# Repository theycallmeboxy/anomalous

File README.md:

# Anomalous Keyboard

## Features

- Integrated STM32 Microcontroller
  
- 42 Key Alice-ish Ortho Layout

- Red Dragon Low Profile Switches

- Solder Only

## Repository Contents

- `pcb/`: KiCAD and production files (bom is missing part numbers)

## Status

- Prototype 1 PCBs ordered 3/15/2024
- Prototype 1 PCBs received 3/20/2024

**DISCLAIMER: I'm not a doctor.  This is not medical advice.  I'm also only a network engineer.  You assume all liability in using or reproducing these files.**

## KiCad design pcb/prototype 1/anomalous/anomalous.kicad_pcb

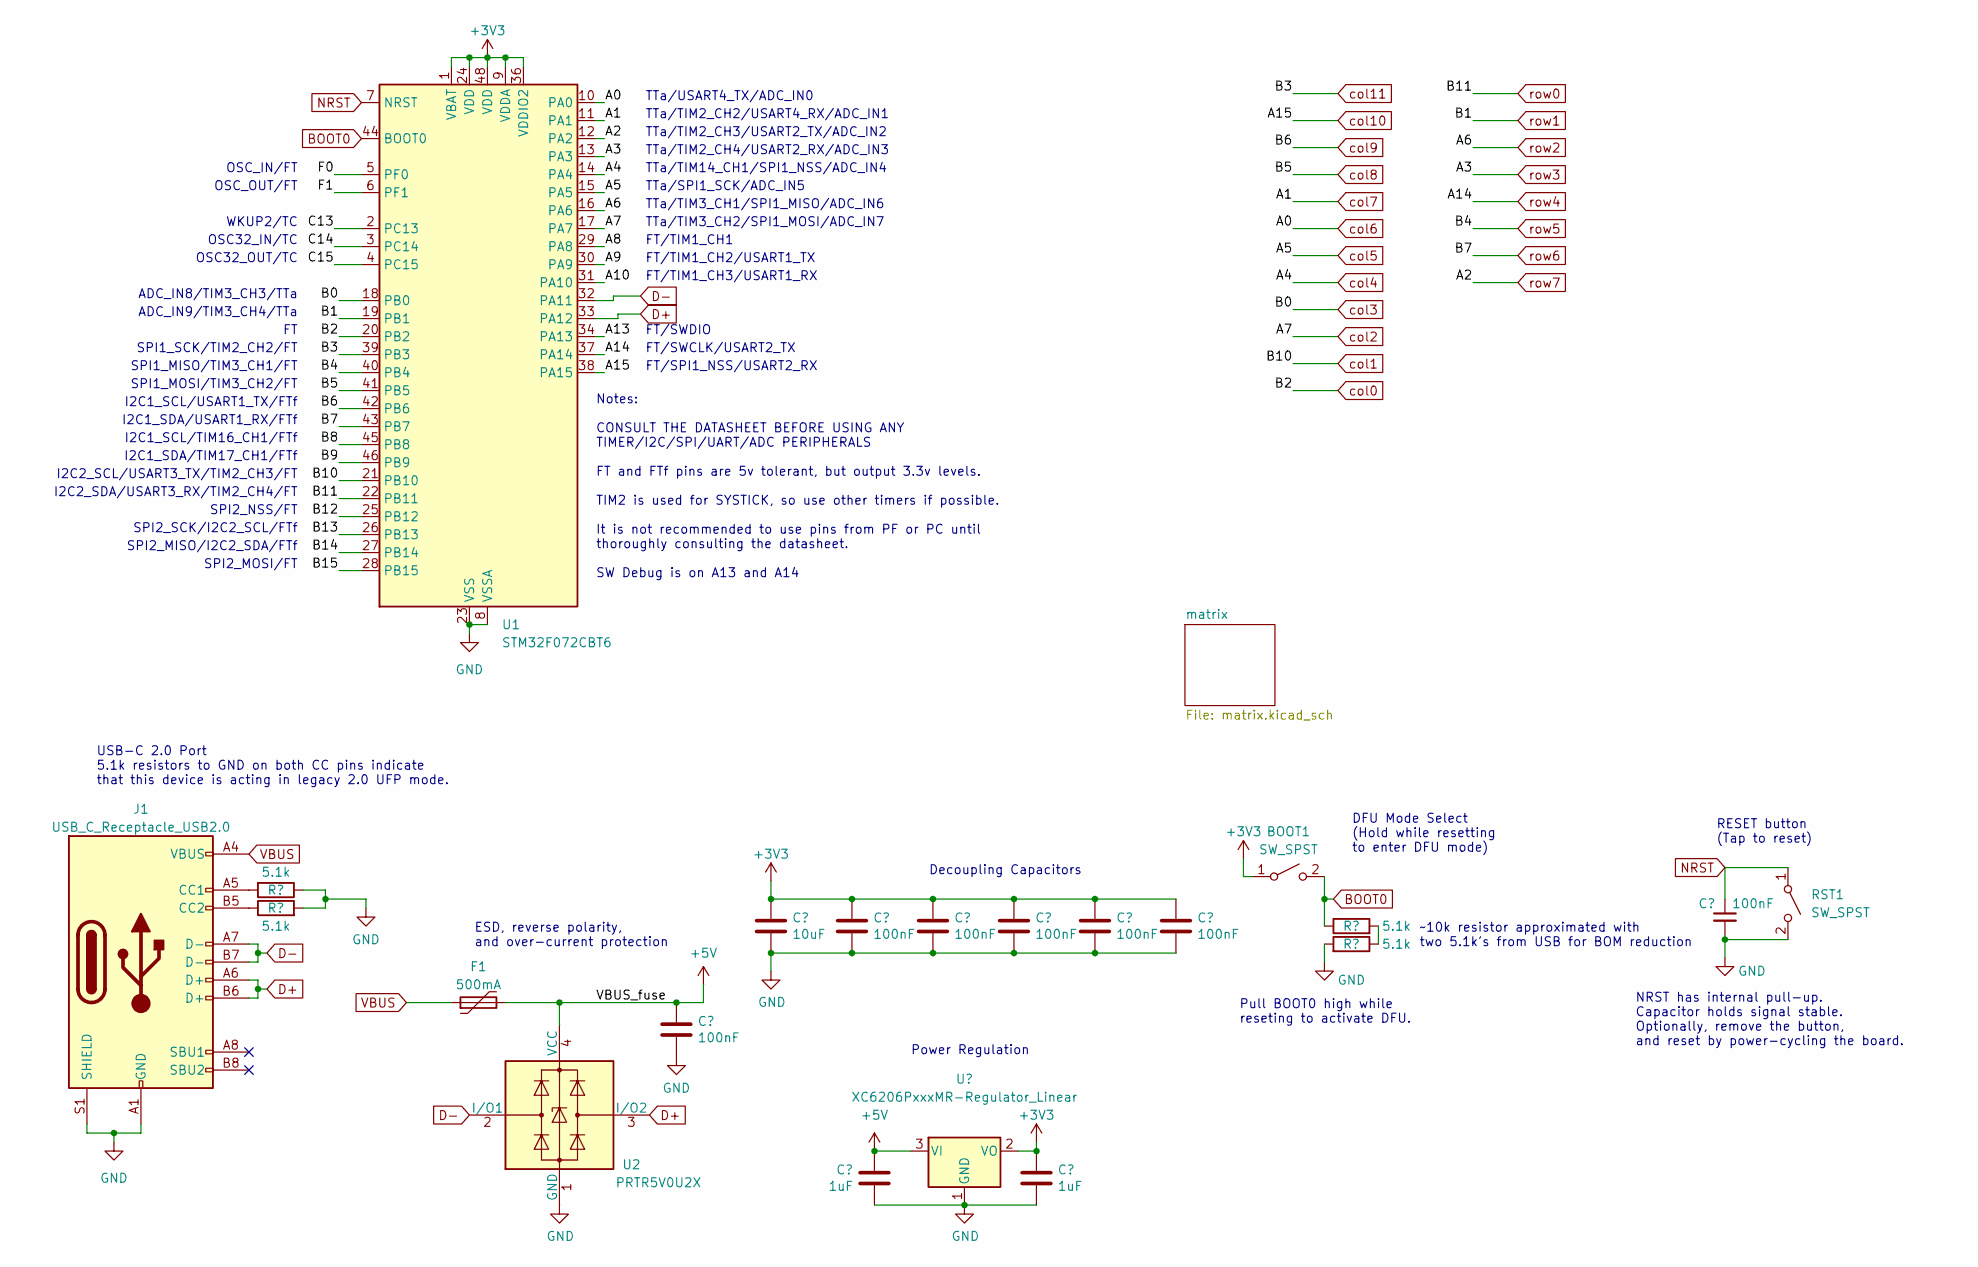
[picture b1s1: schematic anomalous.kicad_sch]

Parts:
BOOT1: SW_SPST; SW_SPST_TL3342
C1, C3, C4, C5, C6, C7, C8: 100nF; C_0402_1005Metric; LCSC C307331
C2: 10uF; C_0603_1608Metric; LCSC C307331
C9, C10: 1uF; C_0402_1005Metric; LCSC C307331
F1: 500mA; Fuse_1206_3216Metric; LCSC C135341
J1: USB_C_Receptacle_USB2.0; USB_C_Receptacle_HRO_TYPE-C-31-M-12; JlcRotOffset 180
R1, R2, R3, R4: 5.1k; R_0402_1005Metric
RST1: SW_SPST; SW_SPST_TL3342
U1: STM32F072CBT6; LQFP-48_7x7mm_P0.5mm; JlcRotOffset 90
U2: PRTR5V0U2X; SOT-143; LCSC C2827688
U3: XC6206PxxxMR-Regulator_Linear; SOT-23; LCSC C5446

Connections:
+3V3: BOOT1.1 (A), C2.1, C3.1, C4.1, C5.1, C6.1, C7.1, C10.1, U1.1 (VBAT), U1.9 (VDDA), U1.24 (VDD), U1.36 (VDDIO2), U1.48 (VDD), U3.2 (VO)
+5V: C8.1, C9.1, F1.2, U2.4 (VCC), U3.3 (VI)
/A8: U1.29 (PA8)
/A9: U1.30 (PA9)
/A10: U1.31 (PA10)
/A13: U1.34 (PA13)
/B8: U1.45 (PB8)
/B9: U1.46 (PB9)
/B12: U1.25 (PB12)
/B13: U1.26 (PB13)
/B14: U1.27 (PB14)
/B15: U1.28 (PB15)
/C13: U1.2 (PC13)
/C14: U1.3 (PC14)
/C15: U1.4 (PC15)
/F0: U1.5 (PF0)
/F1: U1.6 (PF1)
BOOT0: BOOT1.2 (B), R3.1, U1.44 (BOOT0)
D+: J1.A6 (D+), J1.B6 (D+), U1.33 (PA12), U2.3 (I/O2)
D-: J1.A7 (D-), J1.B7 (D-), U1.32 (PA11), U2.2 (I/O1)
GND: C1.2, C2.2, C3.2, C4.2, C5.2, C6.2, C7.2, C8.2, C9.2, C10.2, J1.A1 (GND), J1.A12 (GND), J1.B1 (GND), J1.B12 (GND), J1.S1 (SHIELD), R1.1, R2.2, R4.2, RST1.2 (B), U1.8 (VSSA), U1.23 (VSS), U1.35 (VSS), U1.47 (VSS), U2.1 (GND), U3.1 (GND)
NRST: C1.1, RST1.1 (A), U1.7 (NRST)
unnamed: J1.A5 (CC1), R1.2
unnamed: J1.B5 (CC2), R2.1
unnamed: R3.2, R4.1
VBUS: F1.1, J1.A4 (VBUS), J1.A9 (VBUS), J1.B4 (VBUS), J1.B9 (VBUS)
col0: U1.20 (PB2); also elsewhere on the board
col1: U1.21 (PB10); also elsewhere on the board
col2: U1.17 (PA7); also elsewhere on the board
col3: U1.18 (PB0); also elsewhere on the board
col4: U1.14 (PA4); also elsewhere on the board
col5: U1.15 (PA5); also elsewhere on the board
col6: U1.10 (PA0); also elsewhere on the board
col7: U1.11 (PA1); also elsewhere on the board
col8: U1.41 (PB5); also elsewhere on the board
col9: U1.42 (PB6); also elsewhere on the board
col10: U1.38 (PA15); also elsewhere on the board
col11: U1.39 (PB3); also elsewhere on the board
row0: U1.22 (PB11); also elsewhere on the board
row1: U1.19 (PB1); also elsewhere on the board
row2: U1.16 (PA6); also elsewhere on the board
row3: U1.13 (PA3); also elsewhere on the board
row4: U1.37 (PA14); also elsewhere on the board
row5: U1.40 (PB4); also elsewhere on the board
row6: U1.43 (PB7); also elsewhere on the board
row7: U1.12 (PA2); also elsewhere on the board

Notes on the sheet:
SPI1_SCK/TIM2_CH2/FT
FT/TIM1_CH1
FT/TIM1_CH3/USART1_RX
SPI2_NSS/FT
Notes: CONSULT THE DATASHEET BEFORE USING ANY TIMER/I2C/SPI/UART/ADC PERIPHERALS FT and FTf pins are 5v tolerant, but output 3.3v levels. TIM2 is used for SYSTICK, so use other timers if possible. It is not recommended to use pins from PF or PC until thoroughly consulting the datasheet. SW Debug is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
TTa/TIM2_CH4/USART2_RX/ADC_IN3
NRST has internal pull-up. Capacitor holds signal stable. Optionally, remove the button, and reset by power-cycling the board.
FT/SWDIO
Decoupling Capacitors
SPI1_MOSI/TIM3_CH2/FT
ADC_IN9/TIM3_CH4/TTa
I2C2_SCL/USART3_TX/TIM2_CH3/FT
SPI2_MISO/I2C2_SDA/FTf
FT/SWCLK/USART2_TX
I2C1_SCL/TIM16_CH1/FTf
~10k resistor approximated with two 5.1k's from USB for BOM reduction
TTa/TIM2_CH2/USART4_RX/ADC_IN1
USB-C 2.0 Port 5.1k resistors to GND on both CC pins indicate that this device is acting in legacy 2.0 UFP mode.
TTa/TIM2_CH3/USART2_TX/ADC_IN2
OSC_IN/FT
DFU Mode Select (Hold while resetting to enter DFU mode)
WKUP2/TC
I2C2_SDA/USART3_RX/TIM2_CH4/FT
ADC_IN8/TIM3_CH3/TTa
RESET button (Tap to reset)
Pull BOOT0 high while reseting to activate DFU.
I2C1_SDA/TIM17_CH1/FTf
TTa/SPI1_SCK/ADC_IN5
TTa/TIM3_CH1/SPI1_MISO/ADC_IN6
TTa/TIM3_CH2/SPI1_MOSI/ADC_IN7
OSC32_OUT/TC
FT/SPI1_NSS/USART2_RX
SPI1_MISO/TIM3_CH1/FT
OSC32_IN/TC
TTa/TIM14_CH1/SPI1_NSS/ADC_IN4
I2C1_SDA/USART1_RX/FTf
SPI2_MOSI/FT
FT/TIM1_CH2/USART1_TX
Power Regulation
SPI2_SCK/I2C2_SCL/FTf

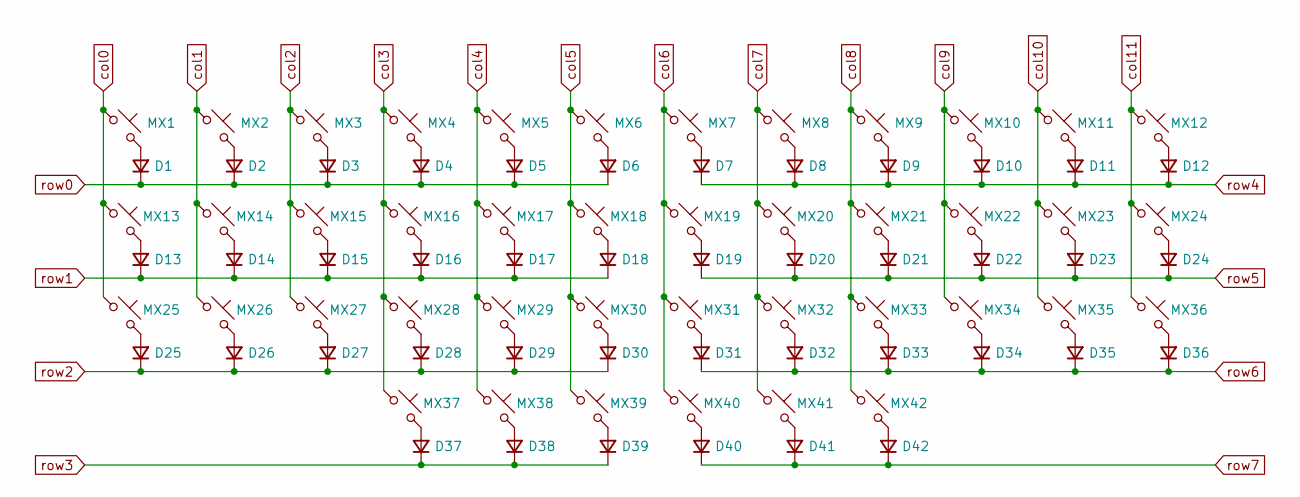
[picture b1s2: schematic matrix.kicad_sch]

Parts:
D1, D2, D3, D4, D5, D6, D7, D8, D9, D10, D11, D12, D13, D14, D15, D16, D17, D18, D19, D20, D21, D22, D23, D24, D25, D26, D27, D28, D29, D30, D31, D32, D33, D34, D35, D36, D37, D38, D39, D40, D41, D42: D_Small; D_SOD-123
MX1, MX2, MX3, MX4, MX5, MX6, MX7, MX8, MX9, MX10, MX11, MX12, MX13, MX14, MX15, MX16, MX17, MX18, MX19, MX20, MX21, MX22, MX23, MX24, MX25, MX26, MX27, MX28, MX29, MX30, MX31, MX32, MX33, MX34, MX35, MX36, MX37, MX38, MX39, MX40, MX41, MX42: MX_SW_solder; SW_Redragon_LowProfile_PCB_1.00u

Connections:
unnamed: D1.2 (A), MX1.2
unnamed: D2.2 (A), MX2.2
unnamed: D3.2 (A), MX3.2
unnamed: D4.2 (A), MX4.2
unnamed: D5.2 (A), MX5.2
unnamed: D6.2 (A), MX6.2
unnamed: D7.2 (A), MX7.2
unnamed: D8.2 (A), MX8.2
unnamed: D9.2 (A), MX9.2
unnamed: D10.2 (A), MX10.2
unnamed: D11.2 (A), MX11.2
unnamed: D12.2 (A), MX12.2
unnamed: D13.2 (A), MX13.2
unnamed: D14.2 (A), MX14.2
unnamed: D15.2 (A), MX15.2
unnamed: D16.2 (A), MX16.2
unnamed: D17.2 (A), MX17.2
unnamed: D18.2 (A), MX18.2
unnamed: D19.2 (A), MX19.2
unnamed: D20.2 (A), MX20.2
unnamed: D21.2 (A), MX21.2
unnamed: D22.2 (A), MX22.2
unnamed: D23.2 (A), MX23.2
unnamed: D24.2 (A), MX24.2
unnamed: D25.2 (A), MX25.2
unnamed: D26.2 (A), MX26.2
unnamed: D27.2 (A), MX27.2
unnamed: D28.2 (A), MX28.2
unnamed: D29.2 (A), MX29.2
unnamed: D30.2 (A), MX30.2
unnamed: D31.2 (A), MX31.2
unnamed: D32.2 (A), MX32.2
unnamed: D33.2 (A), MX33.2
unnamed: D34.2 (A), MX34.2
unnamed: D35.2 (A), MX35.2
unnamed: D36.2 (A), MX36.2
unnamed: D37.2 (A), MX37.2
unnamed: D38.2 (A), MX38.2
unnamed: D39.2 (A), MX39.2
unnamed: D40.2 (A), MX40.2
unnamed: D41.2 (A), MX41.2
unnamed: D42.2 (A), MX42.2
col0: MX1.1, MX13.1, MX25.1; also elsewhere on the board
col1: MX2.1, MX14.1, MX26.1; also elsewhere on the board
col2: MX3.1, MX15.1, MX27.1; also elsewhere on the board
col3: MX4.1, MX16.1, MX28.1, MX37.1; also elsewhere on the board
col4: MX5.1, MX17.1, MX29.1, MX38.1; also elsewhere on the board
col5: MX6.1, MX18.1, MX30.1, MX39.1; also elsewhere on the board
col6: MX7.1, MX19.1, MX31.1, MX40.1; also elsewhere on the board
col7: MX8.1, MX20.1, MX32.1, MX41.1; also elsewhere on the board
col8: MX9.1, MX21.1, MX33.1, MX42.1; also elsewhere on the board
col9: MX10.1, MX22.1, MX34.1; also elsewhere on the board
col10: MX11.1, MX23.1, MX35.1; also elsewhere on the board
col11: MX12.1, MX24.1, MX36.1; also elsewhere on the board
row0: D1.1 (K), D2.1 (K), D3.1 (K), D4.1 (K), D5.1 (K), D6.1 (K); also elsewhere on the board
row1: D13.1 (K), D14.1 (K), D15.1 (K), D16.1 (K), D17.1 (K), D18.1 (K); also elsewhere on the board
row2: D25.1 (K), D26.1 (K), D27.1 (K), D28.1 (K), D29.1 (K), D30.1 (K); also elsewhere on the board
row3: D37.1 (K), D38.1 (K), D39.1 (K); also elsewhere on the board
row4: D7.1 (K), D8.1 (K), D9.1 (K), D10.1 (K), D11.1 (K), D12.1 (K); also elsewhere on the board
row5: D19.1 (K), D20.1 (K), D21.1 (K), D22.1 (K), D23.1 (K), D24.1 (K); also elsewhere on the board
row6: D31.1 (K), D32.1 (K), D33.1 (K), D34.1 (K), D35.1 (K), D36.1 (K); also elsewhere on the board
row7: D40.1 (K), D41.1 (K), D42.1 (K); also elsewhere on the board

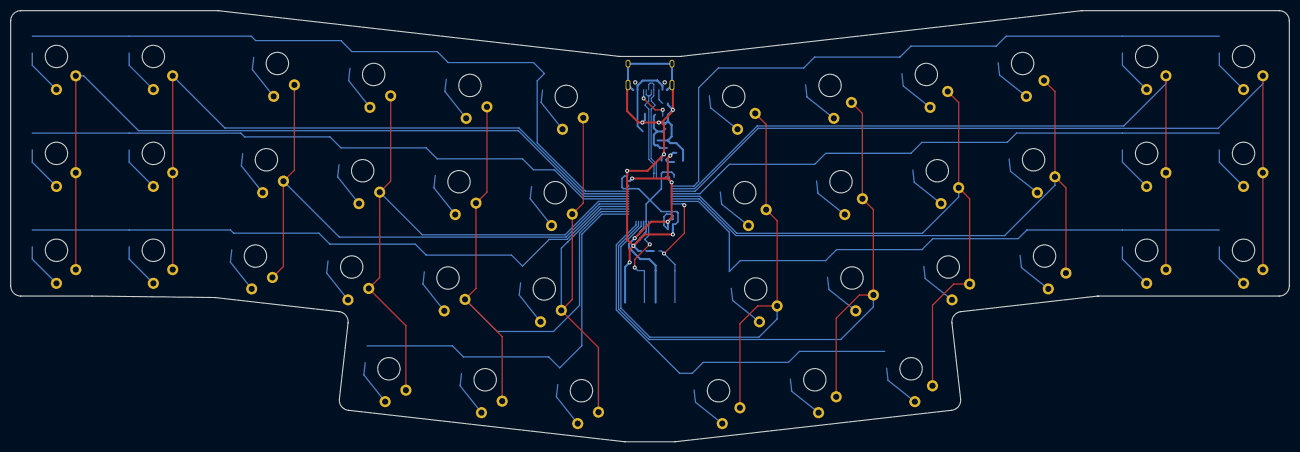
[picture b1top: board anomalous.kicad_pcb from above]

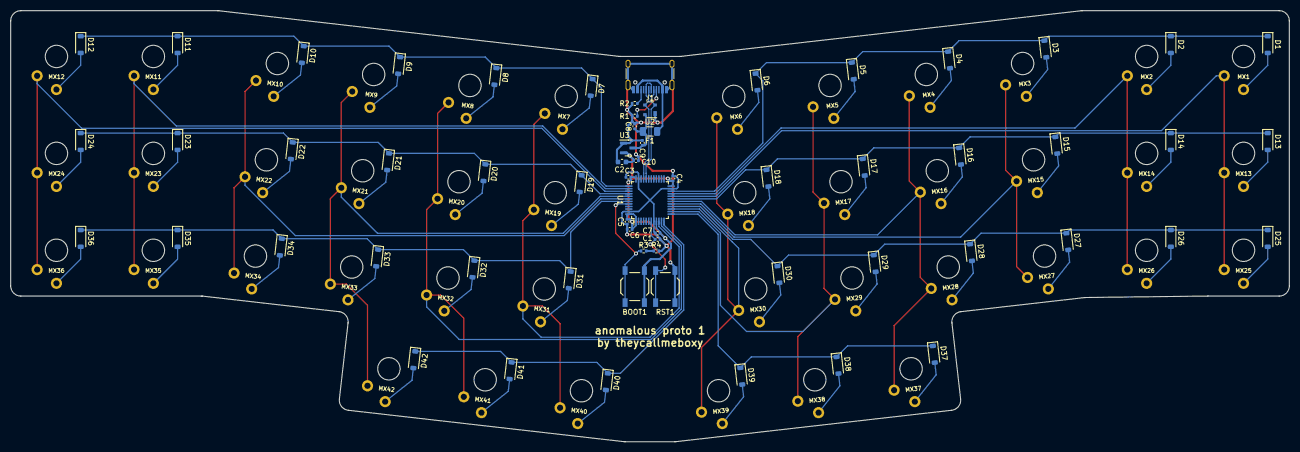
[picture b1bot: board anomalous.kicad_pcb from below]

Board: 2 copper layers, 251.4 x 84.7 mm, 105 parts (63 on the bottom side), 73 nets.

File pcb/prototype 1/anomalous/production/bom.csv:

Designator,Footprint,Quantity,Value,LCSC Part #
"BOOT1, RST1",SW_SPST_TL3342,2,SW_SPST,
"C1, C3, C4, C5, C6, C7, C8",0402,7,100nF,C307331
"C10, C9",0402,2,1uF,C307331
C2,0603,1,10uF,C307331
"D1, D10, D11, D12, D13, D14, D15, D16, D17, D18, D19, D2, D20, D21, D22, D23, D24, D25, D26, D27, D28, D29, D3, D30, D31, D32, D33, D34, D35, D36, D37, D38, D39, D4, D40, D41, D42, D5, D6, D7, D8, D9",D_SOD-123,42,D_Small,
F1,1206,1,500mA,C135341
J1,USB_C_Receptacle_HRO_TYPE-C-31-M-12,1,USB_C_Receptacle_USB2.0,
"MX1, MX10, MX11, MX12, MX13, MX14, MX15, MX16, MX17, MX18, MX19, MX2, MX20, MX21, MX22, MX23, MX24, MX25, MX26, MX27, MX28, MX29, MX3, MX30, MX31, MX32, MX33, MX34, MX35, MX36, MX37, MX38, MX39, MX4, MX40, MX41, MX42, MX5, MX6, MX7, MX8, MX9",SW_Redragon_LowProfile_PCB_1.00u-naked,42,MX_SW_solder,
"R1, R2, R3, R4",0402,4,5.1k,
U1,LQFP-48_7x7mm_P0.5mm,1,STM32F072CBT6,
U2,SOT-143,1,PRTR5V0U2X,C2827688
U3,SOT-23,1,XC6206PxxxMR-Regulator_Linear,C5446

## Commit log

2024-03-16 Housekeeping
